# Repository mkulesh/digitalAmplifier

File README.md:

# digitalAmplifier
Class-D amplifier with MCU controll

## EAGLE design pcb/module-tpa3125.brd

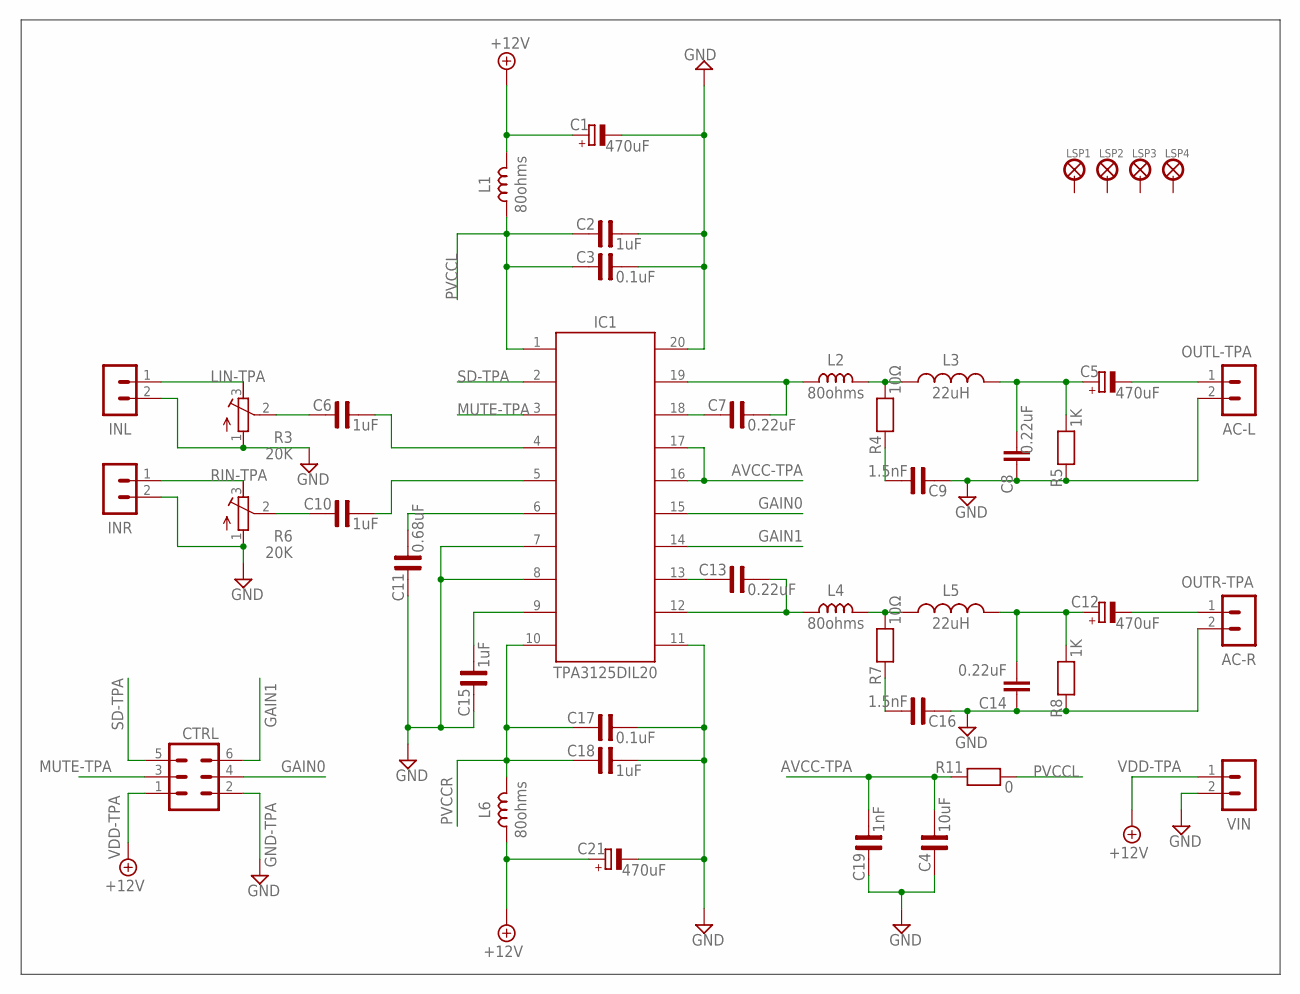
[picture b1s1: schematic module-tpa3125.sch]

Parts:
AC-L: MA02-1GREEN; MA02-1-GREEN
AC-R: MA02-1GREEN; MA02-1-GREEN
C1, C5, C12, C21: 470uF; E5-10,5
C2, C6, C10, C18: 1uF; C1206
C3, C17: 0.1uF; C0805
C4: 10uF; C0805
C7, C13: 0.22uF; C0805
C8, C14: 0.22uF; C050-050X075
C9, C16: 1.5nF; C0805
C11: 0.68uF; C0805
C15: 1uF; C0805
C19: 1nF; C0805
CTRL: MA03-2
IC1: TPA3125DIL20; DIL20
INL: MA02-1GREEN; MA02-1-GREEN
INR: MA02-1GREEN; MA02-1-GREEN
L1, L2, L4, L6: 80ohms; L0805
L3, L5: 22uH; 6000-XXXX-RC
LSP1, LSP2, LSP3, LSP4: LSP27
R3, R6: 20K; PV32H
R4, R7: 10Ω; R0805
R5, R8: 1K; R0805
R11: 0; R0805
VIN: MA02-1GREEN; MA02-1-GREEN

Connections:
AVCC-TPA: C4.2, C19.2, IC1.16, IC1.17, R11.1
GAIN0: CTRL.4, IC1.15
GAIN1: CTRL.6, IC1.14
GND-TPA: AC-L.2, AC-R.2, C1.-, C2.2, C3.2, C4.1, C8.1, C9.1, C11.1, C14.1, C15.1, C16.1, C17.2, C18.2, C19.1, C21.-, CTRL.2, IC1.7, IC1.8, IC1.11, IC1.20, INL.2, INR.2, R3.1, R5.1, R6.1, R8.1, VIN.2
LIN-TPA: INL.1, R3.3
MUTE-TPA: CTRL.3, IC1.3
unnamed: C10.1, R6.2
unnamed: C13.1, IC1.13
unnamed: C6.1, R3.2
unnamed: C6.2, IC1.4
unnamed: C10.2, IC1.5
unnamed: C11.2, IC1.6
unnamed: C15.2, IC1.9
unnamed: C7.1, IC1.18
unnamed: C7.2, IC1.19, L2.1
unnamed: C9.2, R4.1
unnamed: L2.2, L3.1, R4.2
unnamed: C5.+, C8.2, L3.2, R5.2
unnamed: C16.2, R7.1
unnamed: L4.2, L5.1, R7.2
unnamed: C12.+, C14.2, L5.2, R8.2
unnamed: C13.2, IC1.12, L4.1
OUTL-TPA: AC-L.1, C5.-
OUTR-TPA: AC-R.1, C12.-
PVCCL: C2.1, C3.1, IC1.1, L1.1, R11.2
PVCCR: C17.1, C18.1, IC1.10, L6.2
RIN-TPA: INR.1, R6.3
SD-TPA: CTRL.5, IC1.2
VDD-TPA: C1.+, C21.+, CTRL.1, L1.2, L6.1, VIN.1

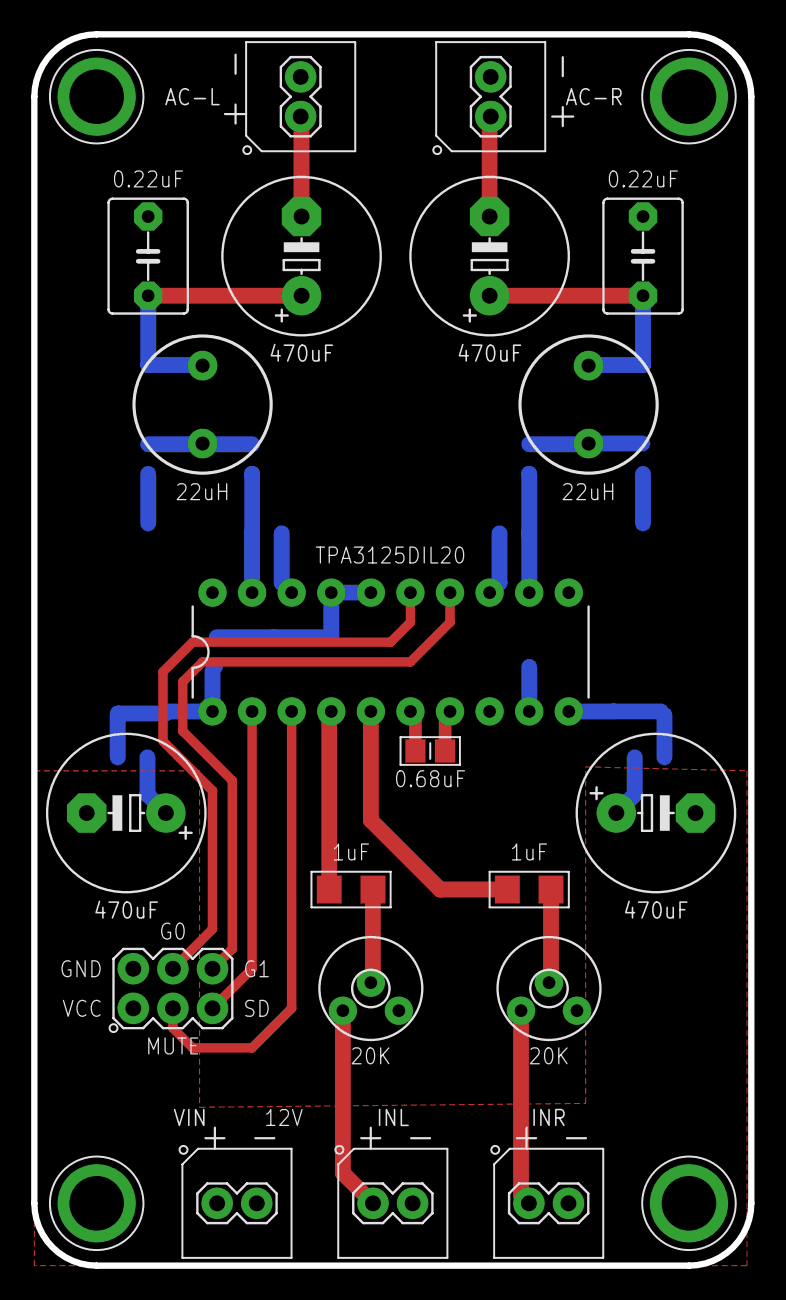
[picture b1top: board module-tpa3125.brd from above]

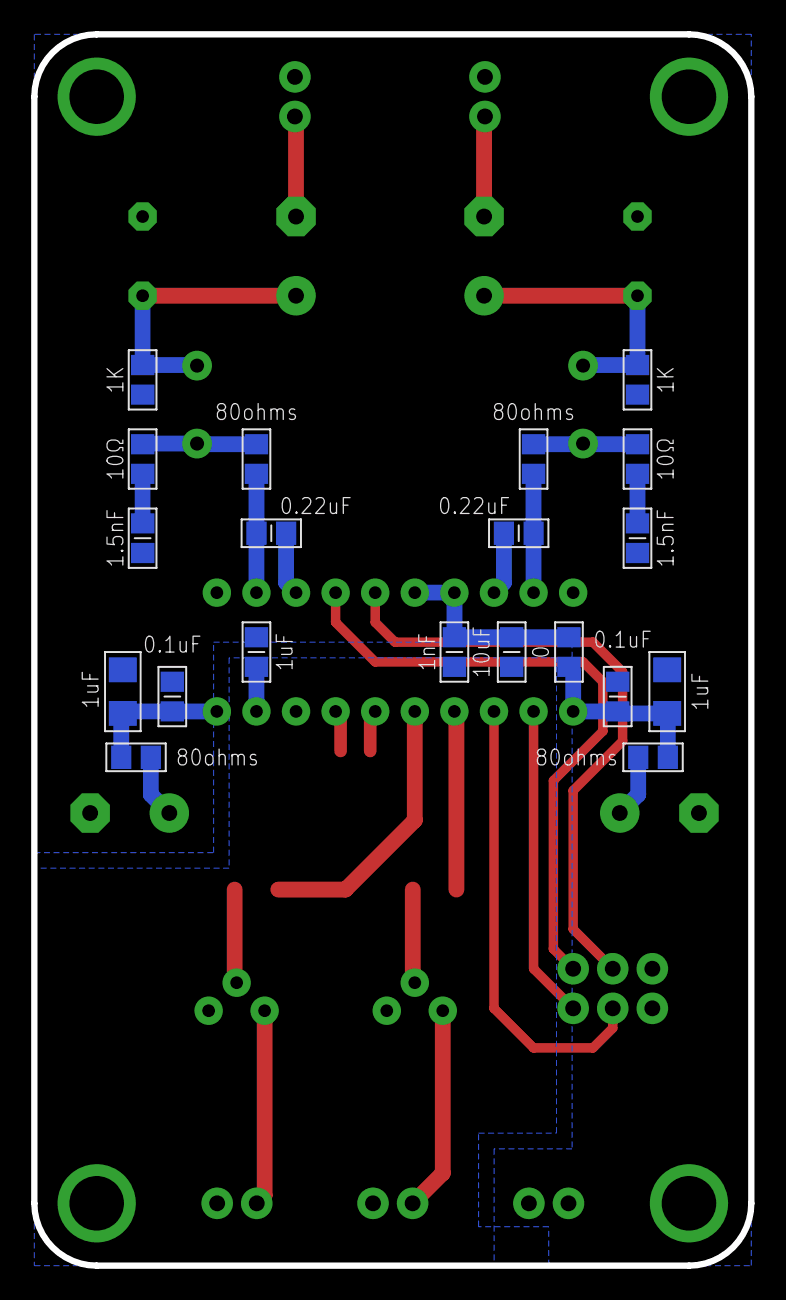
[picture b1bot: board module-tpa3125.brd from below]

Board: 2 copper layers, 46.0 x 79.0 mm, 44 parts (20 on the bottom side), 29 nets.

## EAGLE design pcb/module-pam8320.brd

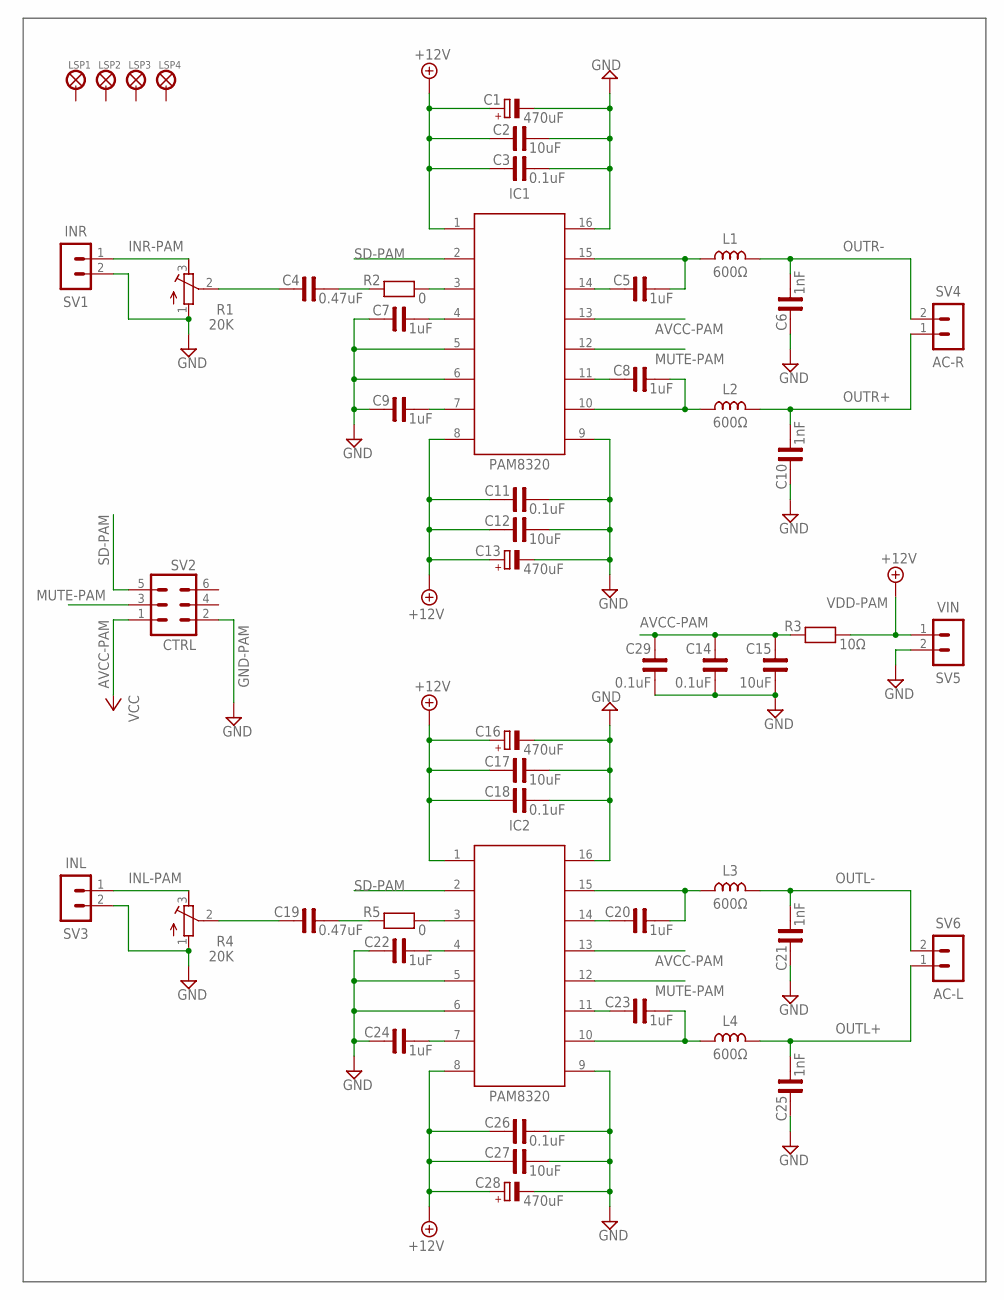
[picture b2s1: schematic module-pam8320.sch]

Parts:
C1, C13, C16, C28: 470uF; E5-10,5
C2, C12, C15, C17, C27: 10uF; C1206
C3, C11, C14, C18, C26, C29: 0.1uF; C0805
C4, C19: 0.47uF; C0805
C5, C7, C8, C9, C20, C22, C23, C24: 1uF; C1206
C6, C10, C21, C25: 1nF; C0805
IC1, IC2: PAM8320; SO16
L1, L2, L3, L4: 600Ω; L1206
LSP1, LSP2, LSP3, LSP4: LSP27
R1, R4: 20K; PV32H
R2, R5: 0; R0805
R3: 10Ω; R0805
SV1: INR; MA02-1-GREEN
SV2: CTRL; MA03-2
SV3: INL; MA02-1-GREEN
SV4: AC-R; MA02-1-GREEN
SV5: VIN; MA02-1-GREEN
SV6: AC-L; MA02-1-GREEN

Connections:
AVCC-PAM: C14.2, C15.2, C29.2, IC1.13, IC2.13, R3.1, SV2.1
GND-PAM: C1.-, C2.2, C3.2, C6.1, C7.1, C9.1, C10.1, C11.2, C12.2, C13.-, C14.1, C15.1, C16.-, C17.2, C18.2, C21.1, C22.1, C24.1, C25.1, C26.2, C27.2, C28.-, C29.1, IC1.5, IC1.6, IC1.9, IC1.16, IC2.5, IC2.6, IC2.9, IC2.16, R1.1, R4.1, SV1.2, SV2.2, SV3.2, SV5.2
INL-PAM: R4.3, SV3.1
INR-PAM: R1.3, SV1.1
MUTE-PAM: IC1.12, IC2.12, SV2.3
unnamed: IC1.3, R2.2
unnamed: C4.1, R1.2
unnamed: C22.2, IC2.4
unnamed: C4.2, R2.1
unnamed: C24.2, IC2.7
unnamed: C5.1, IC1.14
unnamed: C7.2, IC1.4
unnamed: C9.2, IC1.7
unnamed: C5.2, IC1.15, L1.1
unnamed: C8.1, IC1.11
unnamed: C8.2, IC1.10, L2.1
unnamed: C19.1, R4.2
unnamed: IC2.3, R5.2
unnamed: C19.2, R5.1
unnamed: C20.1, IC2.14
unnamed: C20.2, IC2.15, L3.1
unnamed: C23.1, IC2.11
unnamed: C23.2, IC2.10, L4.1
OUTL+: C25.2, L4.2, SV6.1
OUTL-: C21.2, L3.2, SV6.2
OUTR+: C10.2, L2.2, SV4.1
OUTR-: C6.2, L1.2, SV4.2
SD-PAM: IC1.2, IC2.2, SV2.5
VDD-PAM: C1.+, C2.1, C3.1, C11.1, C12.1, C13.+, C16.+, C17.1, C18.1, C26.1, C27.1, C28.+, IC1.1, IC1.8, IC2.1, IC2.8, R3.2, SV5.1

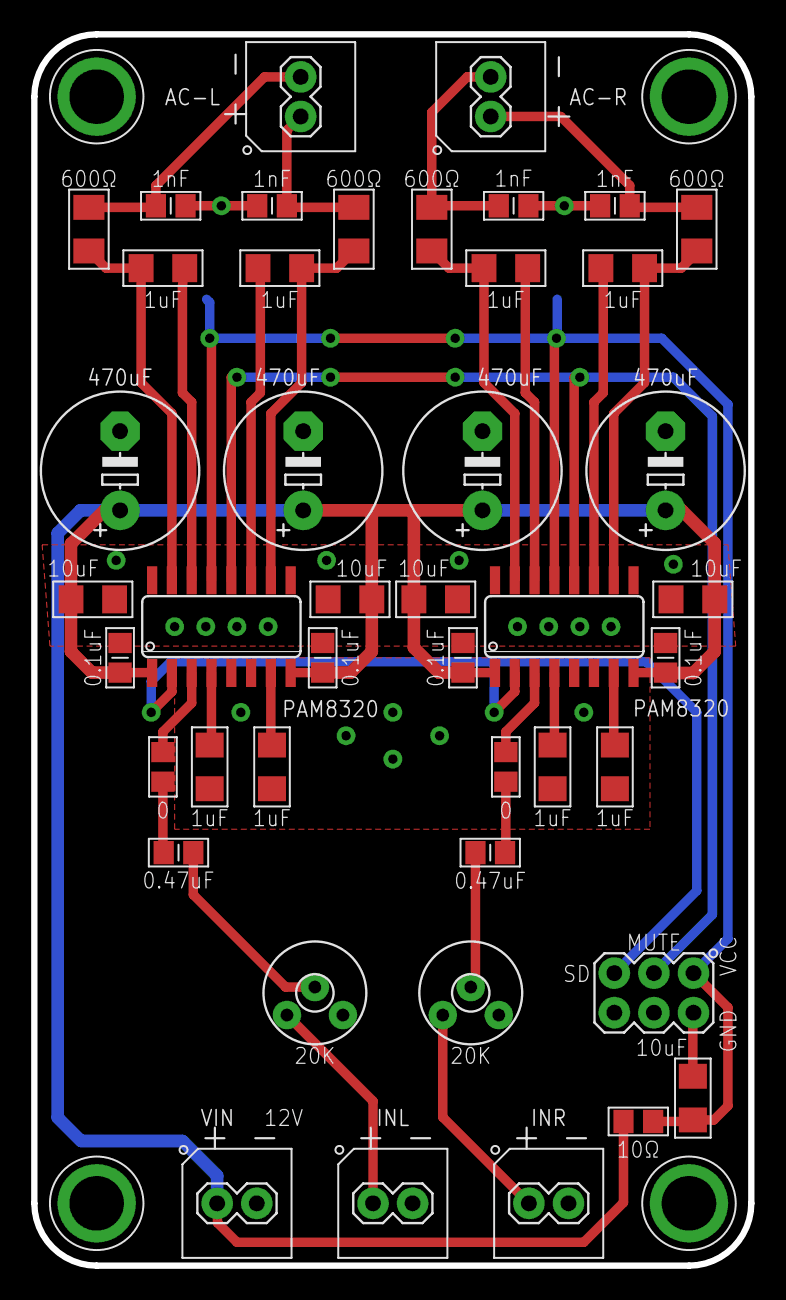
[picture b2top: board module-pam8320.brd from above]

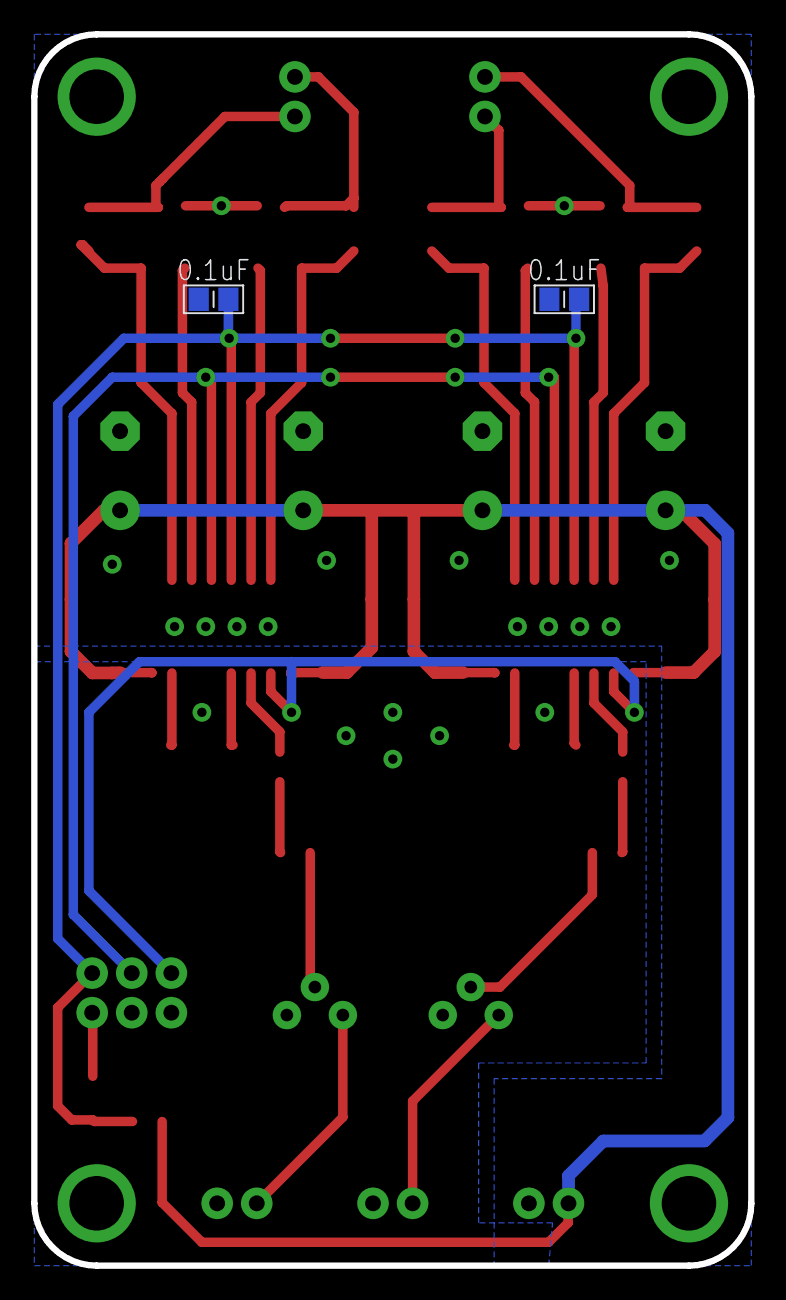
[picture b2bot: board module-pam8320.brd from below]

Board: 2 copper layers, 46.0 x 79.0 mm, 50 parts (2 on the bottom side), 29 nets.

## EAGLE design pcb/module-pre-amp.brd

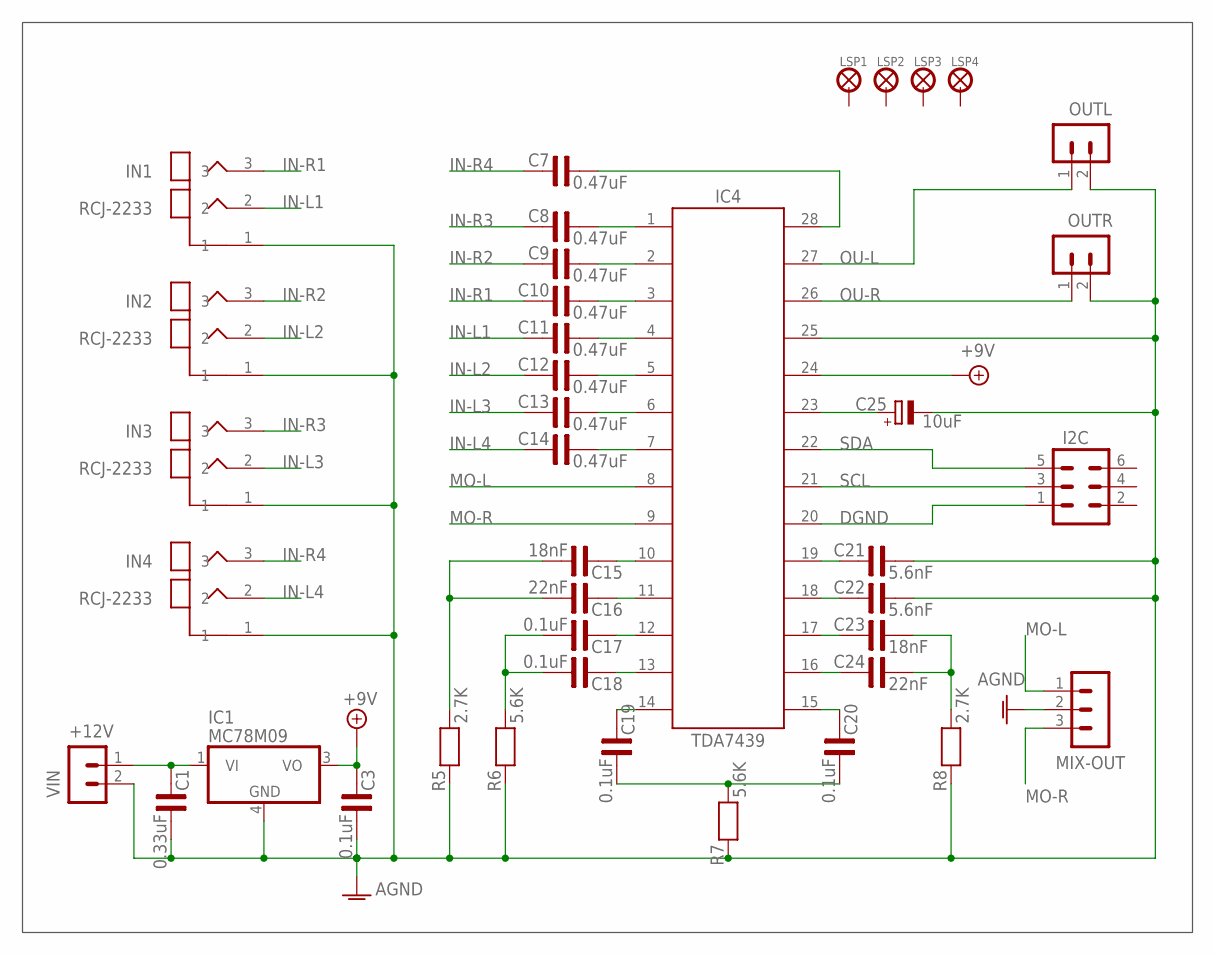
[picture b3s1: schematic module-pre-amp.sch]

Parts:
C1: 0.33uF; C1206
C3: 0.1uF; C1206
C7, C8, C9, C10, C11, C12, C13, C14: 0.47uF; C0805
C15, C23: 18nF; C0805
C16, C24: 22nF; C0805
C17, C18, C19, C20: 0.1uF; C0805
C21, C22: 5.6nF; C0805
C25: 10uF; E2,5-7
I2C: MA03-2
IC1: MC78M09; DPACK_3
IC4: TDA7439; SO28W
IN1, IN2, IN3, IN4: RCJ-2233
LSP1, LSP2, LSP3, LSP4: LSP27
MIX-OUT: MA03-1PL; MA03-1
OUTL: MA02-1GREEN; MA02-1-GREEN
OUTR: MA02-1GREEN; MA02-1-GREEN
R5, R8: 2.7K; R0805
R6, R7: 5.6K; R0805
VIN: MA02-1GREEN; MA02-1-GREEN

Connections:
+12V: C1.1, IC1.1 (VI), VIN.1
AGND: C1.2, C3.2, C21.2, C22.2, C25.-, IC1.4 (GND), IC4.25, IN1.1, IN2.1, IN3.1, IN4.1, MIX-OUT.2, OUTL.2, OUTR.2, R5.1, R6.1, R7.1, R8.1, VIN.2
AVDD: C3.1, IC1.3 (VO), IC4.24
DGND: I2C.1, IC4.20
IN-L1: C11.1, IN1.2
IN-L2: C12.1, IN2.2
IN-L3: C13.1, IN3.2
IN-L4: C14.1, IN4.2
IN-R1: C10.1, IN1.3
IN-R2: C9.1, IN2.3
IN-R3: C8.1, IN3.3
IN-R4: C7.1, IN4.3
MO-L: IC4.8, MIX-OUT.1
MO-R: IC4.9, MIX-OUT.3
unnamed: C25.+, IC4.23
unnamed: C8.2, IC4.1
unnamed: C13.2, IC4.6
unnamed: C14.2, IC4.7
unnamed: C12.2, IC4.5
unnamed: C11.2, IC4.4
unnamed: C10.2, IC4.3
unnamed: C9.2, IC4.2
unnamed: C22.1, IC4.18
unnamed: C21.1, IC4.19
unnamed: C15.1, IC4.10
unnamed: C16.1, IC4.11
unnamed: C7.2, IC4.28
unnamed: C15.2, C16.2, R5.2
unnamed: C17.1, IC4.12
unnamed: C18.1, IC4.13
unnamed: C17.2, C18.2, R6.2
unnamed: C24.1, IC4.16
unnamed: C23.1, IC4.17
unnamed: C23.2, C24.2, R8.2
unnamed: C19.1, IC4.14
unnamed: C20.1, IC4.15
unnamed: C19.2, C20.2, R7.2
OU-L: IC4.27, OUTL.1
OU-R: IC4.26, OUTR.1
SCL: I2C.3, IC4.21
SDA: I2C.5, IC4.22

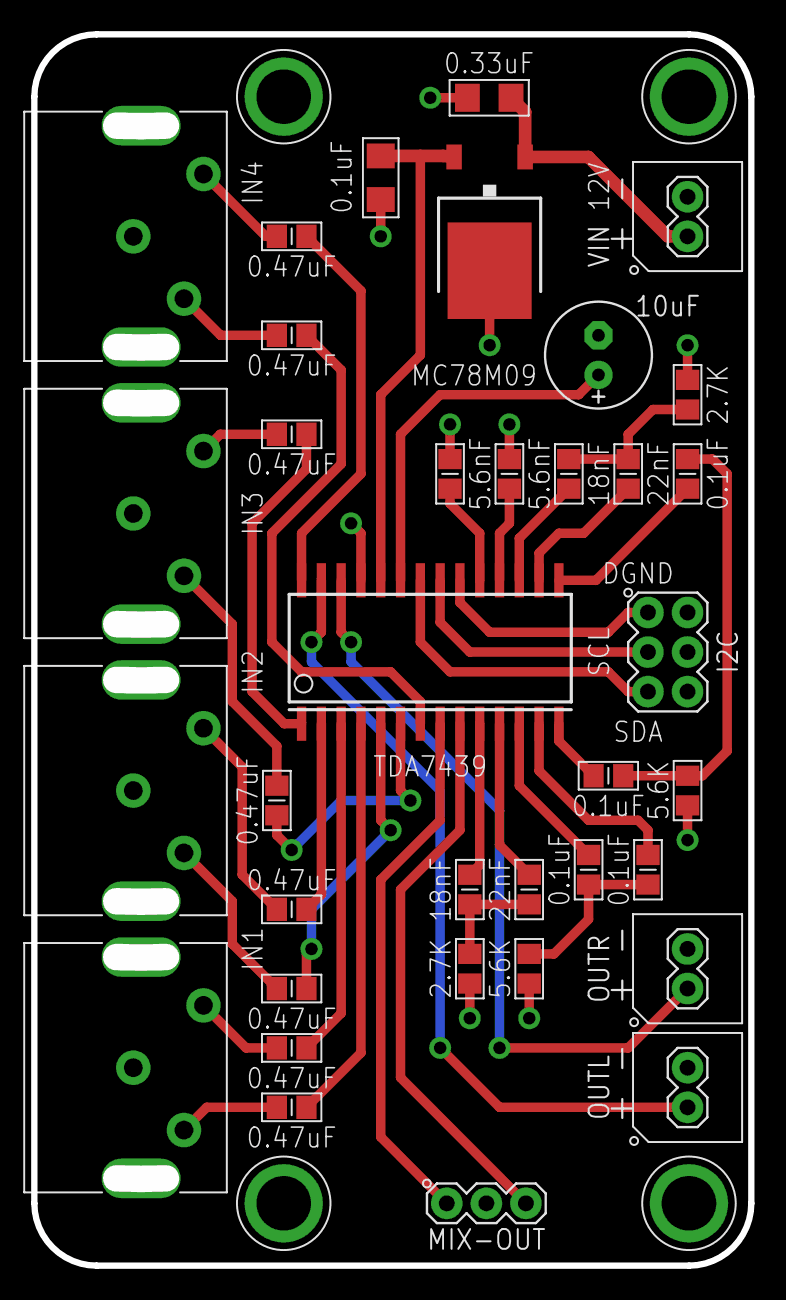
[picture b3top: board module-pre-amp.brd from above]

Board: 2 copper layers, 44.7 x 77.7 mm, 40 parts (0 on the bottom side), 41 nets.

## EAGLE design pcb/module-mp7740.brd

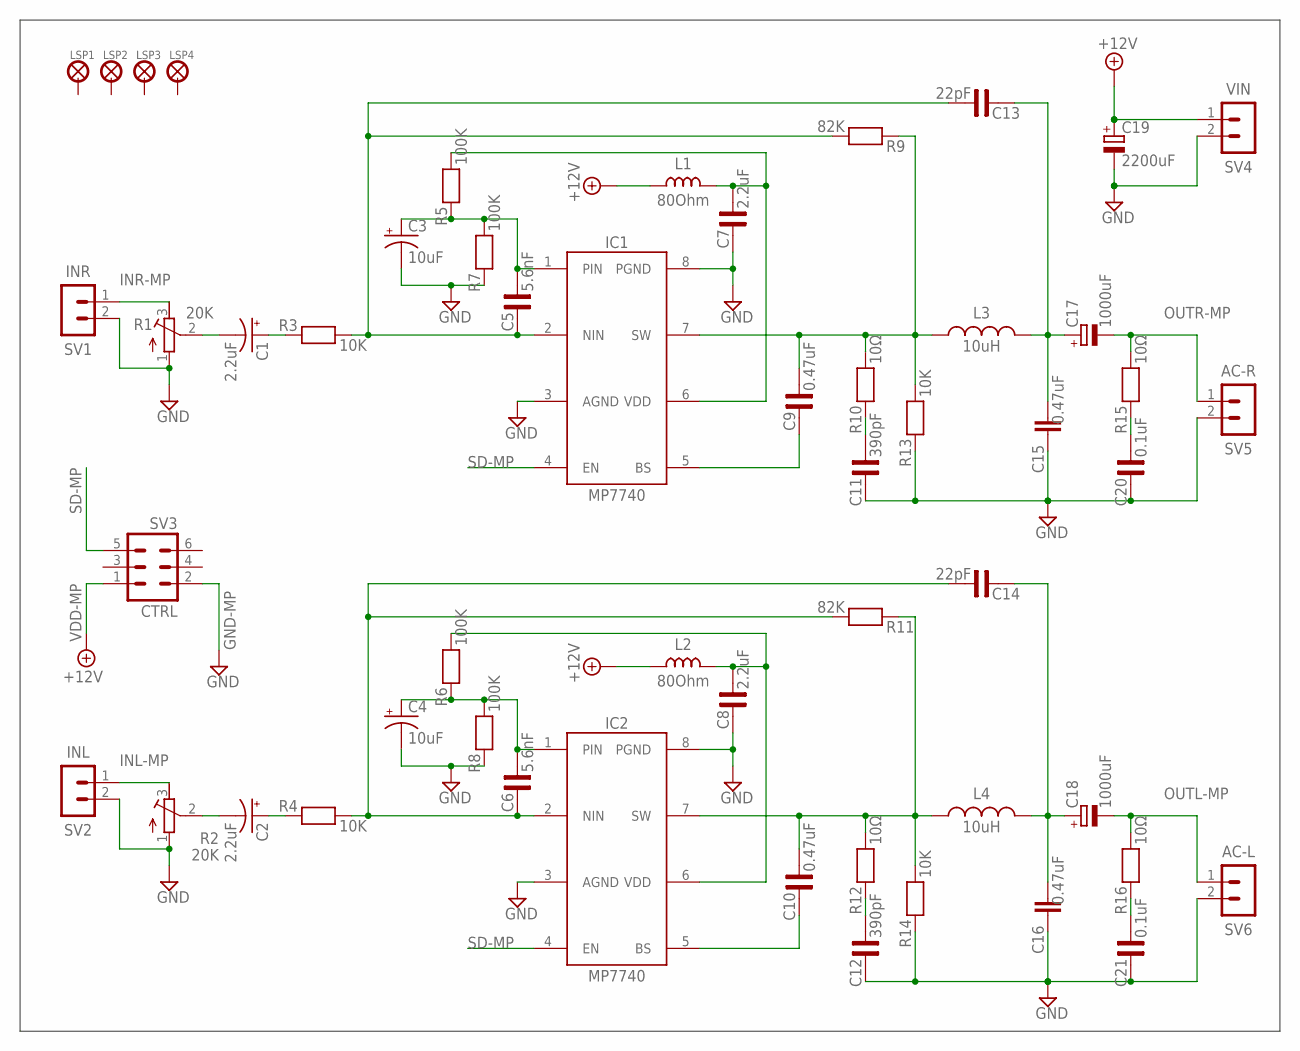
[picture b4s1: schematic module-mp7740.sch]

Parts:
C1, C2: 2.2uF; E2-5
C3, C4: 10uF; E2-5
C5, C6: 5.6nF; C0805
C7, C8: 2.2uF; C1206
C9, C10: 0.47uF; C0805
C11, C12: 390pF; C0805
C13, C14: 22pF; C0805
C15, C16: 0.47uF; C050-050X075
C17, C18: 1000uF; E5-13
C19: 2200uF; E7,5-16
C20, C21: 0.1uF; C0805
IC1, IC2: MP7740; SOIC-8
L1, L2: 80Ohm; L0805
L3, L4: 10uH; 6000-XXXX-RC
LSP1, LSP2, LSP3, LSP4: LSP27
R1, R2: 20K; PV32H
R3, R4, R13, R14: 10K; R0805
R5, R6, R7, R8: 100K; R0805
R9, R11: 82K; R0805
R10, R12, R15, R16: 10Ω; R0805
SV1: INR; MA02-1-GREEN
SV2: INL; MA02-1-GREEN
SV3: CTRL; MA03-2
SV4: VIN; MA02-1-GREEN
SV5: AC-R; MA02-1-GREEN
SV6: AC-L; MA02-1-GREEN

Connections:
GND-MP: C3.-, C4.-, C7.1, C8.1, C11.1, C12.1, C15.1, C16.1, C19.-, C20.1, C21.1, IC1.3 (AGND), IC1.8 (PGND), IC2.3 (AGND), IC2.8 (PGND), R1.1, R2.1, R7.1, R8.1, R13.1, R14.1, SV1.2, SV2.2, SV3.2, SV4.2, SV5.2, SV6.2
INL-MP: R2.3, SV2.1
INR-MP: R1.3, SV1.1
unnamed: C5.1, C13.2, IC1.2 (NIN), R3.2, R9.2
unnamed: C1.+, R3.1
unnamed: C1.-, R1.2
unnamed: C9.2, IC1.7 (SW), L3.1, R9.1, R10.2, R13.2
unnamed: C9.1, IC1.5 (BS)
unnamed: C11.2, R10.1
unnamed: C13.1, C15.2, C17.+, L3.2
unnamed: C20.2, R15.1
unnamed: C6.1, C14.2, IC2.2 (NIN), R4.2, R11.2
unnamed: C3.+, C5.2, IC1.1 (PIN), R5.1, R7.2
unnamed: C2.+, R4.1
unnamed: C10.2, IC2.7 (SW), L4.1, R11.1, R12.2, R14.2
unnamed: C10.1, IC2.5 (BS)
unnamed: C12.2, R12.1
unnamed: C14.1, C16.2, C18.+, L4.2
unnamed: C21.2, R16.1
unnamed: C4.+, C6.2, IC2.1 (PIN), R6.1, R8.2
unnamed: C2.-, R2.2
OUTL-MP: C18.-, R16.2, SV6.1
OUTR-MP: C17.-, R15.2, SV5.1
SD-MP: IC1.4 (EN), IC2.4 (EN), SV3.5
VCCL: C8.2, IC2.6 (VDD), L2.2, R6.2
VCCR: C7.2, IC1.6 (VDD), L1.2, R5.2
VDD-MP: C19.+, L1.1, L2.1, SV3.1, SV4.1

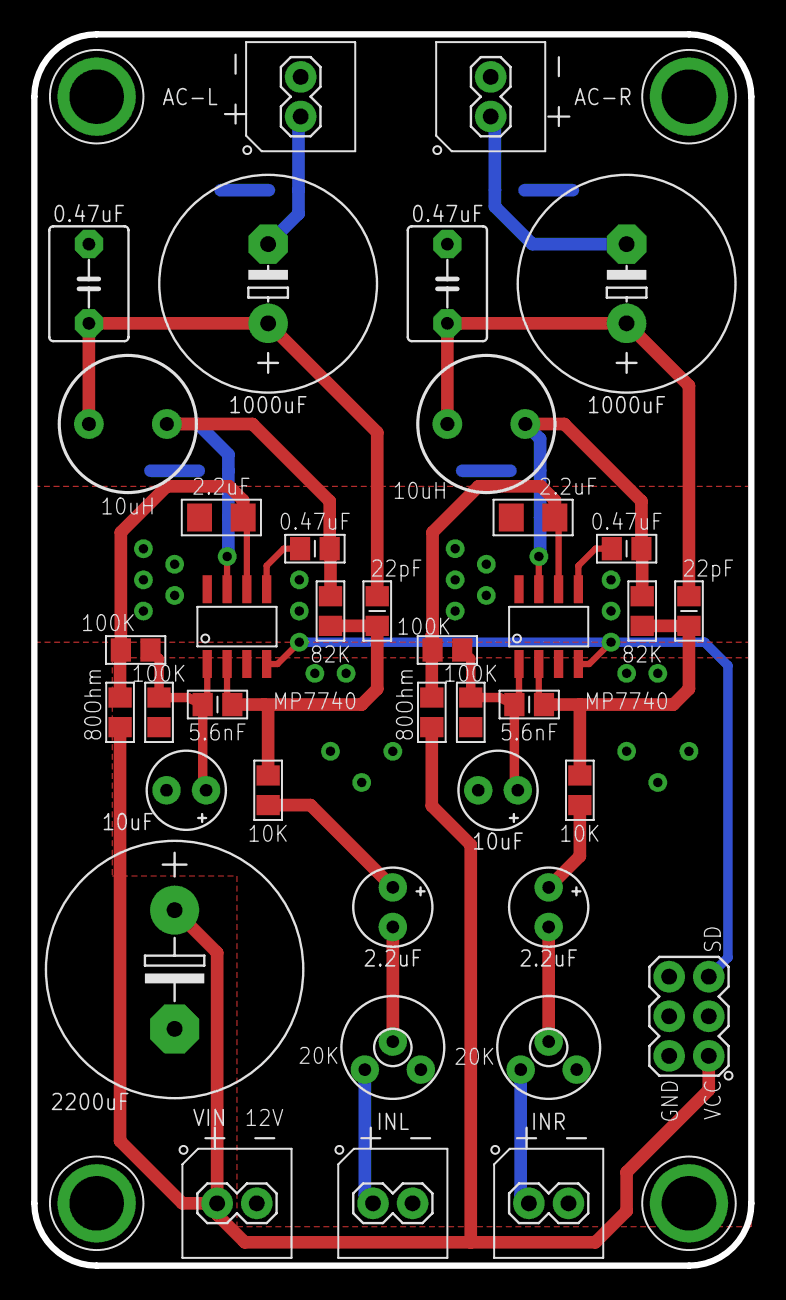
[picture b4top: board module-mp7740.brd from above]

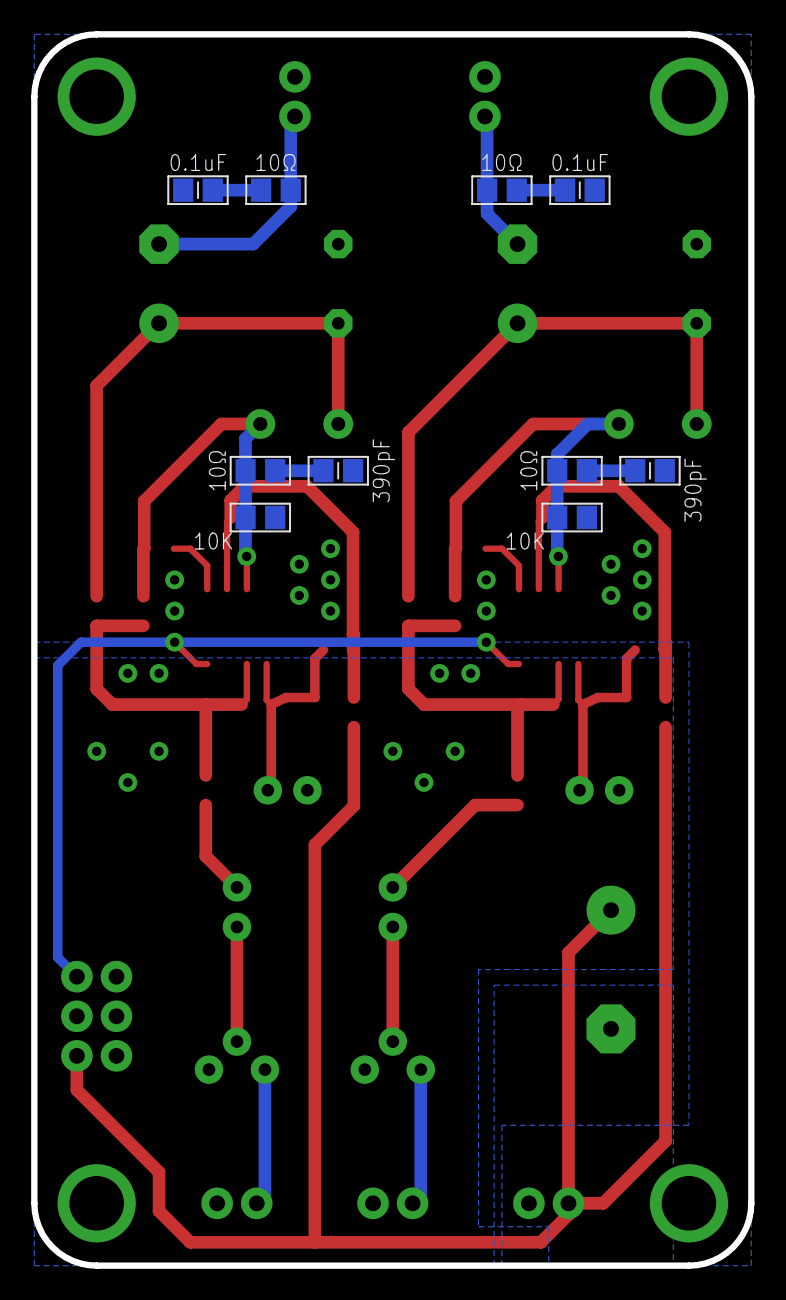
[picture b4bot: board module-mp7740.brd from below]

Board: 2 copper layers, 46.0 x 79.0 mm, 53 parts (10 on the bottom side), 27 nets.
